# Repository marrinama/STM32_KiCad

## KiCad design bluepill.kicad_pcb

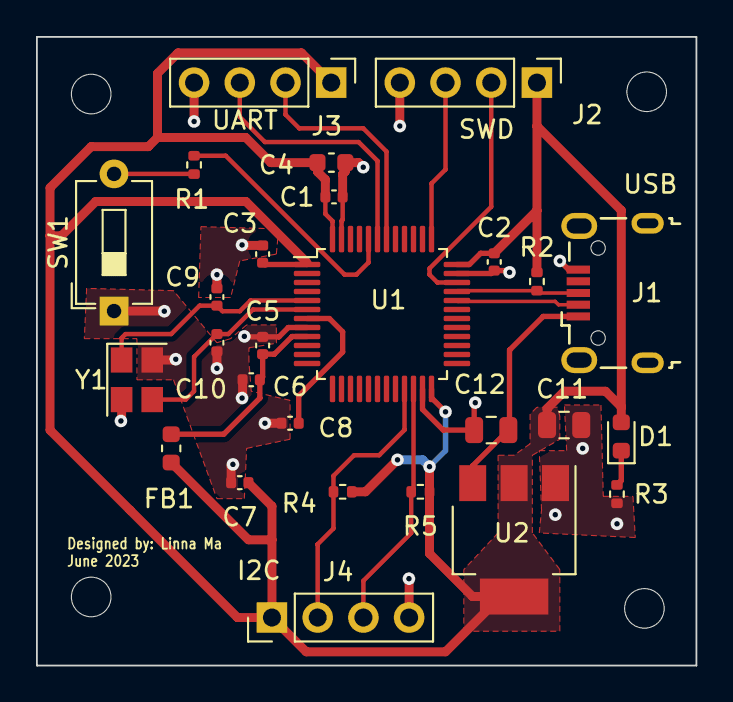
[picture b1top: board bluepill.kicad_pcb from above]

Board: 2 copper layers, 36.6 x 34.9 mm, 31 parts (0 on the bottom side), 18 nets.

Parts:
C1, C2, C3, C8: 100n; C_0402_1005Metric
C4: 10u; C_0603_1608Metric
C5: 10n; C_0402_1005Metric
C6, C7: 1u; C_0402_1005Metric
C9, C10: 10p; C_0402_1005Metric
C11, C12: 22u; C_0805_2012Metric
D1: RED; LED_0603_1608Metric
FB1: FerriteBead; L_0603_1608Metric
H1, H2, H3, H4: MountingHole; MountingHole_2.2mm_M2
J1: USB_B_Micro; USB_Micro-B_Wuerth_629105150521
J2, J3, J4: Conn_01x04_Pin; PinHeader_1x04_P2.54mm_Vertical
R1: 10k; R_0402_1005Metric
R2, R3, R4, R5: 1k5; R_0402_1005Metric
SW1: SW_SPDT; SW_DIP_SPSTx01_Slide_6.7x4.1mm_W7.62mm_P2.54mm_LowProfile
U1: STM32F103C8Tx; LQFP-48_7x7mm_P0.5mm
U2: AMS1117-3.3; SOT-223-3_TabPin2
Y1: 16MHz; Crystal_SMD_3225-4Pin_3.2x2.5mm

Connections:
+3.3V: C1.1, C2.1, C3.1, C4.1, C7.1, C11.1, D1.2 (A), FB1.1, J2.1, J3.1, J4.1, R2.1, R4.1, R5.1, U1.1 (VBAT), U1.24 (VDD), U1.36 (VDD), U1.48 (VDD), U2.2 (VO)
+3.3VA: C5.1, C6.1, FB1.2, U1.9 (VDDA)
/BOOT0: R1.1, U1.44 (BOOT0)
/HSE_IN: C9.1, U1.5 (PD0), Y1.1
/HSE_OUT: C10.1, U1.6 (PD1), Y1.3
/I2C_SCL: J4.2, R4.2, U1.21 (PB10)
/I2C_SDA: J4.3, R5.2, U1.22 (PB11)
/NRST: C8.1, U1.7 (NRST)
/SWCLK: J2.3, U1.37 (PA14)
/SWDIO: J2.2, U1.34 (PA13)
/USART_RX: J3.3, U1.43 (PB7)
/USART_TX: J3.2, U1.42 (PB6)
/USB_D+: J1.3 (D+), R2.2, U1.33 (PA12)
/USB_D-: J1.2 (D-), U1.32 (PA11)
GND: C1.2, C2.2, C3.2, C4.2, C5.2, C6.2, C7.2, C8.2, C9.2, C10.2, C11.2, C12.2, J1.5 (GND), J2.4, J3.4, J4.4, R3.2, SW1.1 (A), U1.8 (VSSA), U1.23 (VSS), U1.35 (VSS), U1.47 (VSS), U2.1 (GND), Y1.2, Y1.4
unnamed: D1.1 (K), R3.1
unnamed: R1.2, SW1.2 (B)
VBUS: C12.1, J1.1 (VBUS), U2.3 (VI)
